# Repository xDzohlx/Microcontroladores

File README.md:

# Microcontroladores
Repositorio de varios códigos para microcontroladores misceláneos y recopilados de algunos controles de hardeware como timers y adc.
Pueden ocuparlos y espero que les sirva.

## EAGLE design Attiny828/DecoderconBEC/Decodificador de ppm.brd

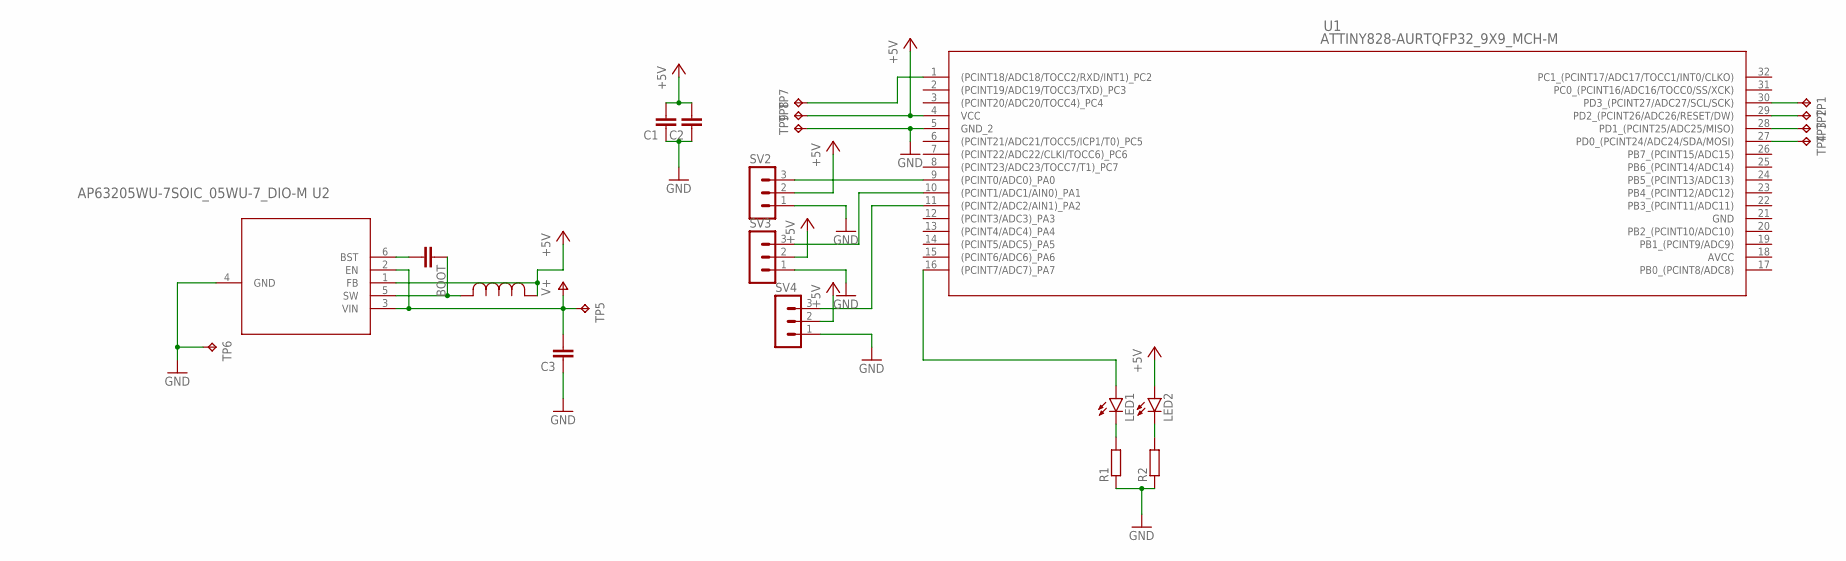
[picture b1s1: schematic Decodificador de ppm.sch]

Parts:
BOOT: C-EUC0402; C0402
C1, C2, C3: C-EUC0805; C0805
LED1, LED2: LEDCHIP-LED0603; CHIP-LED0603
R1, R2: R-EU_R0805; R0805
SV2, SV3, SV4: MA03-1
TP1, TP2, TP3, TP4: TPB1,27; B1,27
TP5, TP6, TP7, TP8, TP9: TPTP19SQ; TP19SQ
U1: ATTINY828-AURTQFP32_9X9_MCH-M; TQFP32_9X9_MCH-M
U2: AP63205WU-7SOIC_05WU-7_DIO-M; SOIC_05WU-7_DIO-M
U$2: INDUCTOR4.7; IND_NRS5030T100MMGJ_TAY

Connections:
+5V: C1.2, C2.2, LED2.A, SV2.2, SV3.2, SV4.2, TP8.TP, U1.4 (VCC), U2.1 (FB), U$2.1
GND: C1.1, C2.1, C3.1, R1.1, R2.1, SV2.1, SV3.1, SV4.1, TP6.TP, TP9.TP, U1.5 (GND_2), U2.4 (GND)
unnamed: LED1.C, R1.2
unnamed: LED2.C, R2.2
unnamed: TP7.TP, U1.1 ((PCINT18/ADC18/TOCC2/RXD/INT1)_PC2)
unnamed: TP1.TP, U1.30 (PD3_(PCINT27/ADC27/SCL/SCK))
unnamed: TP2.TP, U1.29 (PD2_(PCINT26/ADC26/RESET/DW))
unnamed: TP3.TP, U1.28 (PD1_(PCINT25/ADC25/MISO))
unnamed: SV2.3, U1.9 ((PCINT0/ADC0)_PA0)
unnamed: SV3.3, U1.10 ((PCINT1/ADC1/AIN0)_PA1)
unnamed: SV4.3, U1.11 ((PCINT2/ADC2/AIN1)_PA2)
unnamed: TP4.TP, U1.27 (PD0_(PCINT24/ADC24/SDA/MOSI))
unnamed: LED1.A, U1.16 ((PCINT7/ADC7)_PA7)
unnamed: BOOT.1, U2.5 (SW), U$2.2
unnamed: BOOT.2, U2.6 (BST)
V+: C3.2, TP5.TP, U2.2 (EN), U2.3 (VIN)

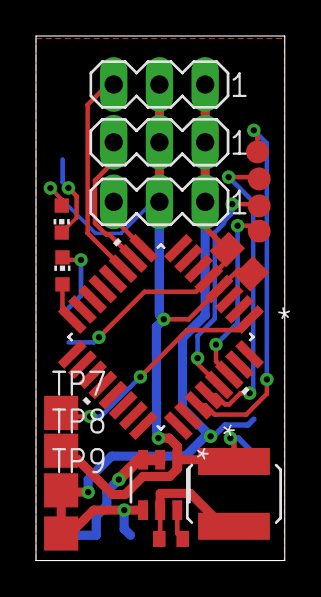
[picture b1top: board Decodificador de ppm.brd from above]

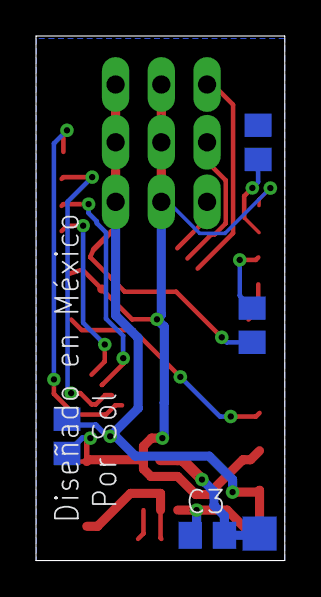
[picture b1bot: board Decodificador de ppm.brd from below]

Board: 2 copper layers, 13.8 x 29.1 mm, 23 parts (5 on the bottom side), 16 nets.

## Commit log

2020-10-08 Create Atmega4808
2020-10-08 Prende y apaga un led, un pin en ente caso PORTA0
2020-10-08 Prende y apaga un led, un pin de 0 a 1
2020-10-09 Create ATSAD10C13A
    Micro de 32 bits
2020-10-09 Prende y apaga un led con un boton
    Código ejemplo
2020-10-10 Actualizado y comentado
2020-10-10 Create Blanco
2020-10-10 Botón que prende y apaga un led
2020-10-18 Create new
2020-10-19 Create sbus.c
    Prueba para lecutra de sbus 100000 bauds e invertido
2020-10-22 Create PWM.c
    Prueba de pwm con rampa sencilla
2020-10-23 Create ADC.c
    Código básico de configuración del ADC del Atmega4808
2020-10-25 Create medidorpwm.c
    Medidor de ancho de pulso mediante sistema de eventos y pwm del timer TCA0 de 16 bits con una resolucion de 10 bits
2020-10-26 Create Attiny828
2020-10-26 Create ppm.c
    Programa básico para lectura de ppm de radiocontrol utiliza 1 timer de 16 bits y la frecuencia de reloj es de 8 MHz con dependencias de Atmel studio
2020-10-26 Create USART.C
    Prueba
2020-10-26 prueba
2020-10-27 Create ATtiny85
2020-10-27 Create PWMservo.c
    De los primeros códigos que hice, justo despues de prender un led y segundo microcontrolador que programe en mi vida encontré el código en un blog perdido al menos se que sirve no es lo mejor pero me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
2020-11-02 Create ATmega4809
2020-11-02 Create Atmega4809.c
    Este mismo código funciona para la serie 0 existe retro compatibilidad
2020-11-02 Update I2C.C
    Ya puede enviar una dirección
2020-12-03 Update ppm.c
    Añade un decodificador antes solo era lectura
2020-12-07 Update ppm.c
    Falto habilitar las interrupciones de cambio de estado el pin PORTA0
2020-12-08 Areglado y probado
    Ya funciona salen canales 1 y 2
2020-12-22 Rename I2C.c to at/I2C.c
2021-01-22 Create Decoder
2021-01-23 funciona
    Probado en la nueva placa con bec
2021-01-27 Add files via upload
    Configuración del ADC sensillo para prender un led con una lectura de aproximadamente 3.6 Volts para un detector de baja bateria de una celda de lipo con alimentacion de 5 volts
2021-02-21 Add files via upload
    Se agrego capcitor de entrada del regulador un canal menos y mejor perfil
2021-07-11 Create PPM.C
    Un pequeño codigo para ller señales de PPM de radiocontrol con este microntrolador utilizando los modos de lectura automatica y el sistema de eventos
2021-08-20 Create RTC.c
    Código para usar el RTC prende y apaga un led mas o menos medio segundo

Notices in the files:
parts and their libraries:
COPYRIGHT: Copyright (C) 2018 Accelerated Designs. All rights reserved
